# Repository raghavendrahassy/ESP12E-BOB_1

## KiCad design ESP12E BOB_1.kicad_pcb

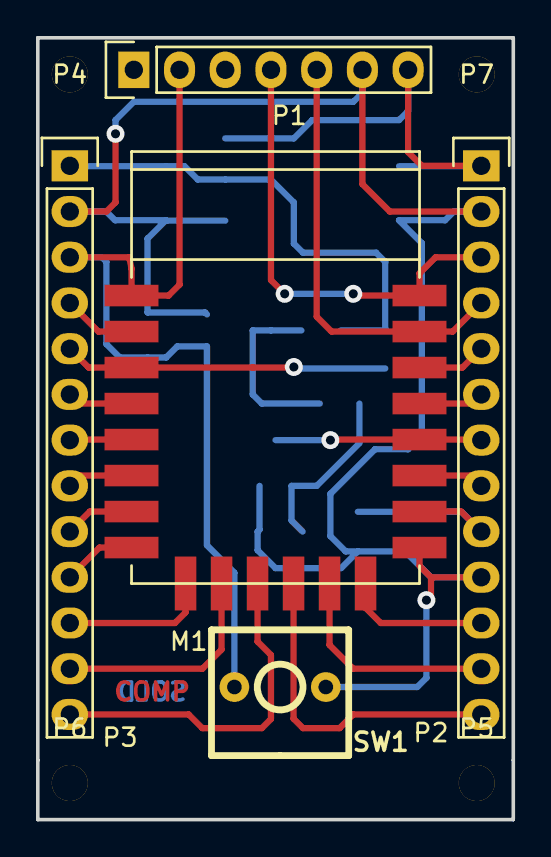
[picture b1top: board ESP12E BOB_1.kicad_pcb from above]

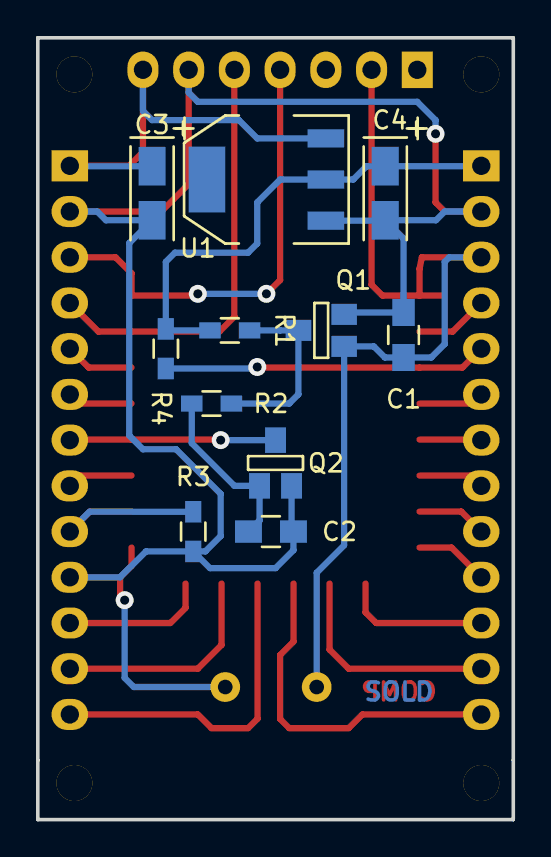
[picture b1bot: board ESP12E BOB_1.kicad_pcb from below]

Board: 2 copper layers, 26.4 x 43.4 mm, 20 parts (11 on the bottom side), 26 nets.

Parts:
C1: 0.1u; C_0805_HandSoldering
C2: 2u2; C_0805_HandSoldering
C3: 4u7; TantalC_SizeA_EIA-3216_Wave
C4: 10u; TantalC_SizeA_EIA-3216_Wave
M1: ESP-12E
P1: CONN_01X07; Pin_Header_Straight_1x07
P2, P3: CONN_01X13; Pin_Header_Straight_1x13
P4, P5, P6, P7: CONN_01X01; 1pin
Q1, Q2: BSS138; SOT-23-GDS
R1: 470K; R_0603_HandSoldering
R2: 100K; R_0603_HandSoldering
R3: 10K; R_0603_HandSoldering
R4: 47K; R_0603_HandSoldering
SW1: SW_PUSH; SW_PUSH_SMALL_2pin_xl
U1: 1117-3.3; SOT-223

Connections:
+3V3: C4.1, P3.1, R1.1, R4.1, U1.2
+5V: C3.1, P1.7, P2.1, U1.3
/DTR: C1.1, M1.1, P1.2, P3.3, Q1.G, SW1.2
/GPIO0: M1.18, P2.7, Q2.D
/GPIO10: M1.12, P2.13
/MOSI: M1.13, P2.12
/RX: M1.22, P1.4, P2.3
/SCK: M1.14, P2.11
/TX: M1.21, P1.5, P2.4
GND: C1.2, C2.2, C3.2, C4.2, M1.15, P1.6, P2.2, P2.10, P3.2, Q1.S, Q2.S, R3.1, SW1.1, U1.1
unnamed: C2.1, Q2.G, R2.1
unnamed: M1.2, P3.4
unnamed: M1.3, P3.5, R4.2
unnamed: M1.4, P3.6
unnamed: M1.5, P3.7
unnamed: M1.6, P3.8
unnamed: M1.7, P3.9
unnamed: M1.8, P3.10
unnamed: M1.9, P3.11
unnamed: M1.10, P3.12
unnamed: M1.11, P3.13
unnamed: M1.16, P2.9, R3.2
unnamed: M1.17, P2.8
unnamed: M1.19, P2.6
unnamed: M1.20, P2.5
unnamed: Q1.D, R1.2, R2.2

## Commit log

2015-06-10 :confetti_ball: Added .gitattributes & .gitignore files
2015-06-10 ESP12E BOB
2015-06-13 ESP12E board test review
